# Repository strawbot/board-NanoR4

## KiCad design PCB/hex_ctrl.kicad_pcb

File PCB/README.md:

# hex_ctrl: KiCad starter project

Generated schematic for the octagonal 24-channel muscle-wire controller (Nano R4 carrier).
Written in KiCad 7 file format so any newer KiCad (including 10) opens it; KiCad will
offer to save in its own format on first save.

## Sheets
- hex_ctrl.kicad_sch  top: Nano R4 (A1), mounting holes H1-H5, sheet links
- power.kicad_sch     supply holes, TVS, reverse-protection P-FET, bulk C, VIN_S divider (refs 1000+)
- logic.kicad_sch     3 x 74HC595 gate-drive chain (OE tied to GND), SCK/RCLK series resistors (refs 1100+)
- imu.kicad_sch       ICM-42688-P on the Nano's 3.3 V I2C bus, SDA/SCL solder pads and SWD access holes (refs 1200+)
- group.kicad_sch     used 3 times (A, B, C): RSENSE + ISNS option, two limb sheets (refs 700/800/900+)
- limb.kicad_sch      used 6 times (L1..L6): 4 channels + 5 wire holes (refs 100..600+)

Group A = limbs L1 + L2, B = L3 + L4, C = L5 + L6.

## Supply and output enable (rev 2)
- The rail after reverse protection is called **VIN** (it was +10V). It is the 21 V test supply; any Vin works as long as
  the parts below are rated for it (see the supply-rating note in the power sheet). VIN_S = Vin x 18k/118k (R1003 is
  18k, was 47k), 3.2 V at 21 V, to ADC A3.
- Supply ratings at 21 V: D1001 is SMAJ24A (24 V standoff; clamps near 39 V, above the 30 V Vds of the AO3401A and
  AO3400A, so it only absorbs moderate surges). C1001 is 100uF 35 V polymer (7343-43 case, same pads as the old
  7343-31); C1002/C1003 are 10uF 50 V X7R 1206 (a 25 V X5R loses most of its capacitance at 21 V; a 22uF 50 V part
  would need a 1210). D1002 (BZT52C10, 10 V zener, gate to source) holds the P-FET's Vgs at -10 V for any Vin; the
  AO3401A is rated +/-12 V. Check the Nano's VIN limit against Vin.
- The keep-alive output-enable circuit (KA, C1104, D1101, D1102, C1105, R1101, R1102, Q1101, JP1101) is gone. OE on all
  three 74HC595s is tied to GND, so the outputs are always enabled; the gate guard on every channel (CAC / RPD / BAT54)
  keeps a stuck-high output from holding a MOSFET on.

## Wire-hole labels
Each limb hole (J101-J601) has its own label (W1-W4, + for Vin) on both silkscreen faces, outboard of the hole between it
and the board edge (generator/silk_limbs.py; rerun it after moving a limb connector). It replaced the old one-string-per-limb
text from the hexagon generator, which was nowhere near the octagon's holes, and the stale "+10V GND" text.

## IMU interrupt
IMU INT1 (3.3 V logic) goes to Nano D2 (5 V logic) through a one-transistor level shifter: Q1201 (2N7002, gate on +3V3)
with R1204 pulling the IMU side up to +3V3 and R1205 pulling the Nano side (IMU_INT_5V) up to +5V. TP1201 stays on the
IMU side. Nano D2 is therefore no longer a spare pin.

## Schematic layout
Each sheet is drawn as a wired, left-to-right flow (protection chain on power, the SER chain and clock trunks on
logic, gate -> R -> C -> FET -> wire hole on each limb), and the top sheet is a block diagram: the Nano, the power,
logic, IMU and group blocks, with every signal (SER, SCK, RCLK, the 24 gate lines, ISNS, VIN_S, UART) drawn as a
wire between blocks. The power rails are shown as a legend on that sheet. The layout comes from
generator/build2.py; generator/README_generator.md describes how it is regenerated and checked against the
original netlist (net for net, pin for pin).

## Design rules
hex_ctrl.kicad_dru (Board Setup > Custom Rules) adds: 0.125 mm pad clearance inside the
IMU footprint only; 0.4 mm min / 0.6 mm preferred width for the supply rail (VIN), GND, VIN_RAW, the wire
nets (W1..W4) and the SRC buses; 0.25 mm for the ISNS sense lines.

## Pre-placed board
hex_ctrl.kicad_pcb is placed and routed (72 mm octagon with the front 7 mm sliced off, 2 layers, 0.8 mm), with every
footprint linked to its schematic symbol and every pad on its net. Open it and press F8
to confirm it matches the schematic. oct_place.py regenerates the placement; hex_place.py
is the retired 63 mm hexagon version, kept for reference. The octagon exists because the
autorouter only routes at 0/45/90 degrees and the 60 degree limbs of the hexagon left 18
wire nets unrouted. The six limbs sit on the edges at 0/45/135/180/225/315 deg; the front
(USB/Nano) and rear edges carry no limb. The front strip holds nothing but the Nano's USB end, so
FRONT_CUT in oct_place.py (7 mm) trims it and the Nano overhangs the board by about 4 mm; its
silkscreen outline in the A1 footprint is left open at that end. 7 mm is the limit: at 8 mm the
limb 3 wire tracks come within 0.39 mm of the new edge (rule 0.5 mm). The cut saves roughly
260 mm2 of board, about 0.4 g.

## Getting to a board (manual route)
1. Open hex_ctrl.kicad_pro. Check the sheets (the text notes flag items to verify).
2. Run Inspect > Electrical Rules Checker. Expected: no errors; unconnected pins are
   marked with no-connect flags.
3. Open the PCB editor, set the board to 2 layers / 0.8 mm (Board Setup), then
   Tools > Update PCB from Schematic (F8).
4. Tools > Scripting Console:  exec(open(r"<path>/hex_place.py").read())
   Draws the hexagon and places every part in its zone (limbs on the edges,
   group parts at their vertices, power at 210 deg,
   IMU at the centre, Nano flipped to the bottom). Checked for courtyard overlaps.

## Board size
oct_place.py uses A = 72 mm across flats. The per-gate guard (CAC + BAT54 on every
channel) made each limb block deeper, and the shorter octagon edges leave less margin at
the vertices; 72 mm placed with the 15 listed courtyard nudges. Change A at the top of
oct_place.py and re-derive the NUDGE table if you resize.

## Designators on the board
Connector (J*) and test point (TP*) designators are on the front silkscreen so they can be read on the
assembled board (generator/silk_designators.py places each at the nearest free spot; rerun it after moving
parts). All other designators and all values stay on F.Fab, which is not part of the manufacturing outputs.
TP1202-TP1208 (the Nano holes) have function labels instead: SCL, SDA, CLK, DIO, RST, GND, 3V3.

## Nano interface (I2C pads, SWD access holes, UART)
J1201 (Qwiic placeholder) was removed. Instead:
- Power and ground come from the Nano castellation: A1 pad 17 (3V3) drives the +3V3 rail,
  pad 4 is GND.
- TP1202 (SCL) and TP1203 (SDA) are 1.6 mm pads with 1.0 mm plated holes
  (hex_ctrl:Nano_Hole_Pad) that sit under the two through-holes either side of the Nano's
  Qwiic connector. Solder a short pin or wire through each hole to the Nano.
- TP1204-TP1208 (SWDIO, SWCLK, NRST, GND, 3V3; silkscreen DIO, CLK, RST, GND, 3V3) are the same
  hole pad, placed over the Nano's SWD test pads. Those pads are on the Nano's underside, which
  faces this board, under the Qwiic connector. Use a pogo pin or solder a wire down the hole
  to reach a pad. SWDIO, SWCLK and NRST have no connection on this board (one-pad nets);
  GND goes to GND, 3V3 to +3V3.
- J1001 is now 1x04: pin 1 VIN_RAW, pin 2 GND, pin 3 TX (Nano D1), pin 4 RX (Nano D0). GND is
  shared with the power input, so pins 2-4 form a GND / TX / RX UART header. Do not plug a
  UART cable onto pins 1-2.

The hole positions come from Arduino's ABX00142 Altium CAD, which is older than the Nano in
hand (its test pad labelled 3V3 is on the +5V net there; measured as 3V3 on the real board).
Measure the real Nano and move TP1202-TP1208 if they differ: mapping and offsets are in
oct_place.py (nano_xy) and generator/nano_iface_pcb.py. The silkscreen labels are board text
from that script. Schematic edits are in generator/nano_iface_sch.py (run once; it edits the
.kicad_sch files in place so footprint links survive).

## Verify before layout
- Nano R4: D9 (RCLK) must be a GPT timer output. D6 (formerly KA) is unused.
- Footprint A1 is hex_ctrl:Arduino_Nano_R4_Castellated (project library): 30 SMD pads
  for soldering the Nano flat on the bottom by its castellated edge. Pad size and offset
  are estimates; check against the real Nano. The Qwiic header placeholder J1201 is gone;
  see "Nano interface" above.
- ICM-42688-P: RESV pins and INT2/FSYNC left unconnected; confirm with the datasheet.
  Confirm the LGA-14 footprint pad order against the datasheet land pattern.
- DNP parts: C701/C801/C901 (ISNS filter), R1202/R1203 (I2C pull-ups).

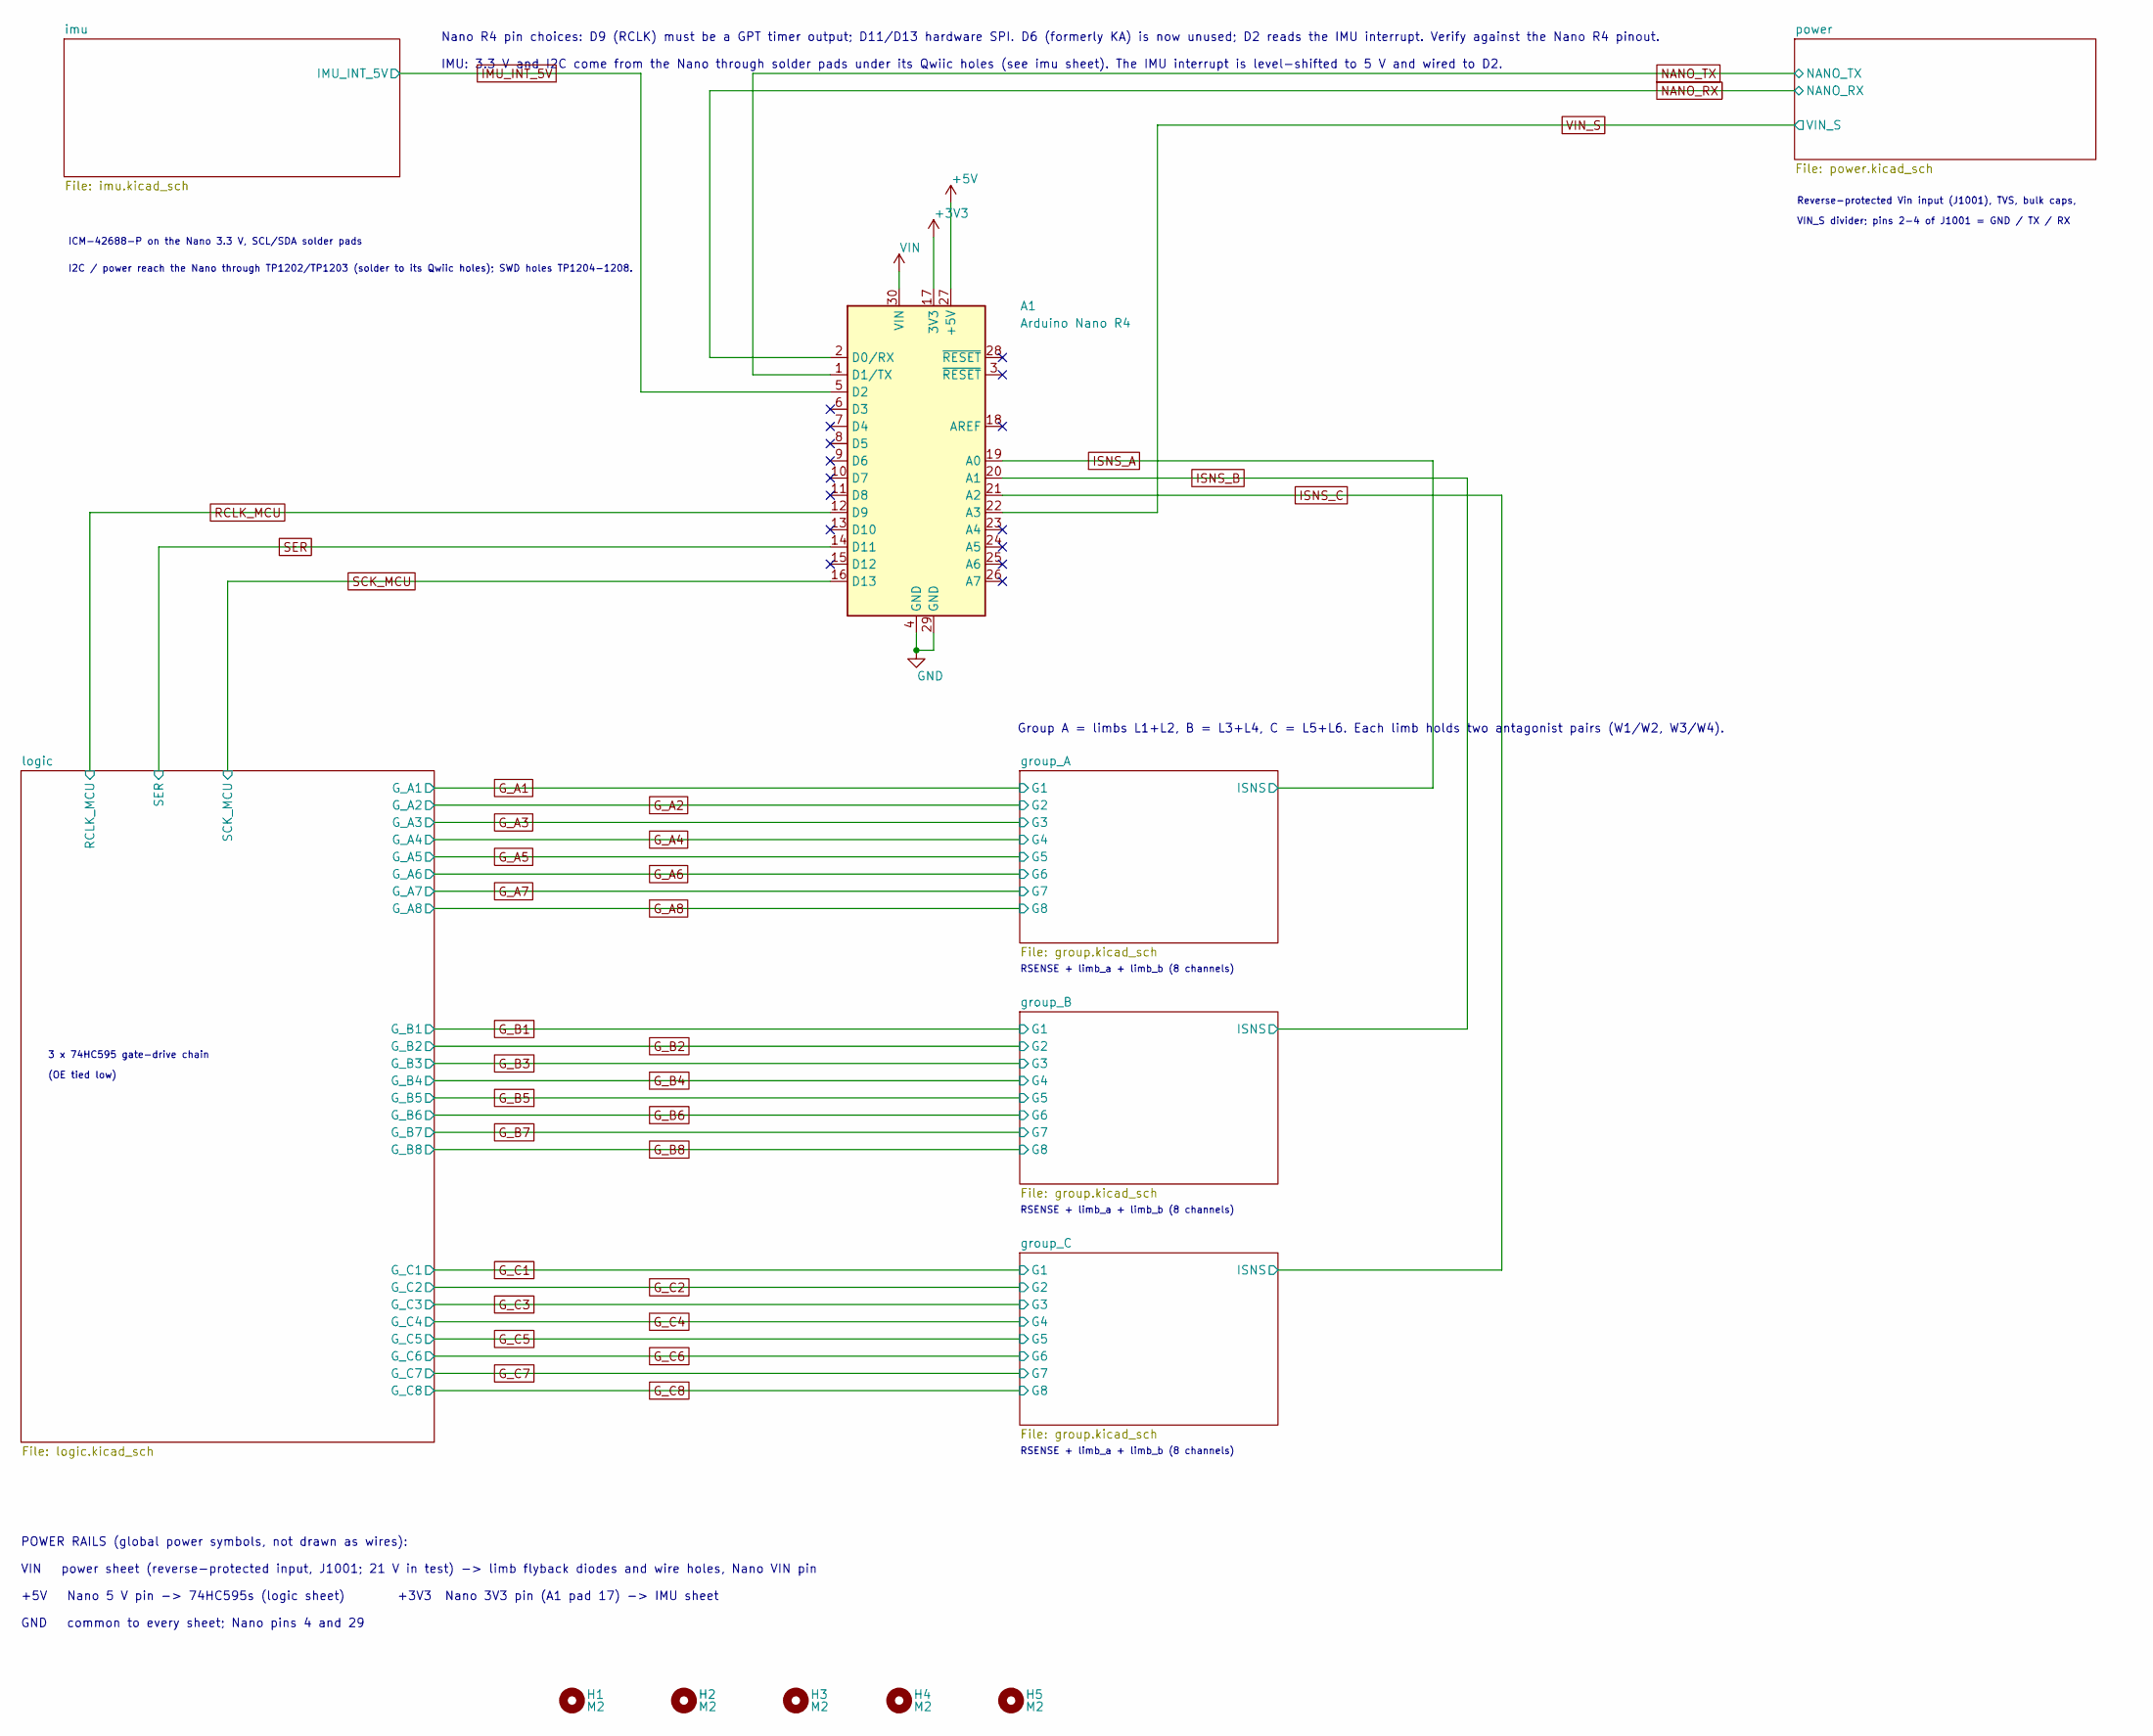
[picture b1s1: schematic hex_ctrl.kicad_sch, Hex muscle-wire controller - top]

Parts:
A1: Arduino Nano R4; Arduino_Nano_R4_Castellated
H1, H2, H3, H4, H5: M2; MountingHole_2.2mm_M2

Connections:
+3V3: A1.17 (3V3); also elsewhere on the board
GND: A1.4 (GND), A1.29 (GND); also elsewhere on the board
IMU_INT_5V: A1.5 (D2); also elsewhere on the board
ISNS_A: A1.19 (A0); also elsewhere on the board
ISNS_B: A1.20 (A1); also elsewhere on the board
ISNS_C: A1.21 (A2); also elsewhere on the board
NANO_RX: A1.2 (D0/RX); also elsewhere on the board
NANO_TX: A1.1 (D1/TX); also elsewhere on the board
RCLK_MCU: A1.12 (D9); also elsewhere on the board
SCK_MCU: A1.16 (D13); also elsewhere on the board
SER: A1.14 (D11); also elsewhere on the board
VIN: A1.30 (VIN); also elsewhere on the board
VIN_S: A1.22 (A3); also elsewhere on the board

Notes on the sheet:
Reverse-protected Vin input (J1001), TVS, bulk caps,
VIN_S divider; pins 2-4 of J1001 = GND / TX / RX
ICM-42688-P on the Nano 3.3 V, SCL/SDA solder pads
3 x 74HC595 gate-drive chain
(OE tied low)
RSENSE + limb_a + limb_b (8 channels)
Nano R4 pin choices: D9 (RCLK) must be a GPT timer output; D11/D13 hardware SPI. D6 (formerly KA) is now unused; D2 reads the IMU interrupt. Verify against the Nano R4 pinout.
IMU: 3.3 V and I2C come from the Nano through solder pads under its Qwiic holes (see imu sheet). The IMU interrupt is level-shifted to 5 V and wired to D2.
I2C / power reach the Nano through TP1202/TP1203 (solder to its Qwiic holes); SWD holes TP1204-1208.
Group A = limbs L1+L2, B = L3+L4, C = L5+L6. Each limb holds two antagonist pairs (W1/W2, W3/W4).
POWER RAILS (global power symbols, not drawn as wires):
VIN power sheet (reverse-protected input, J1001; 21 V in test) -> limb flyback diodes and wire holes, Nano VIN pin
+5V Nano 5 V pin -> 74HC595s (logic sheet) +3V3 Nano 3V3 pin (A1 pad 17) -> IMU sheet
GND common to every sheet; Nano pins 4 and 29

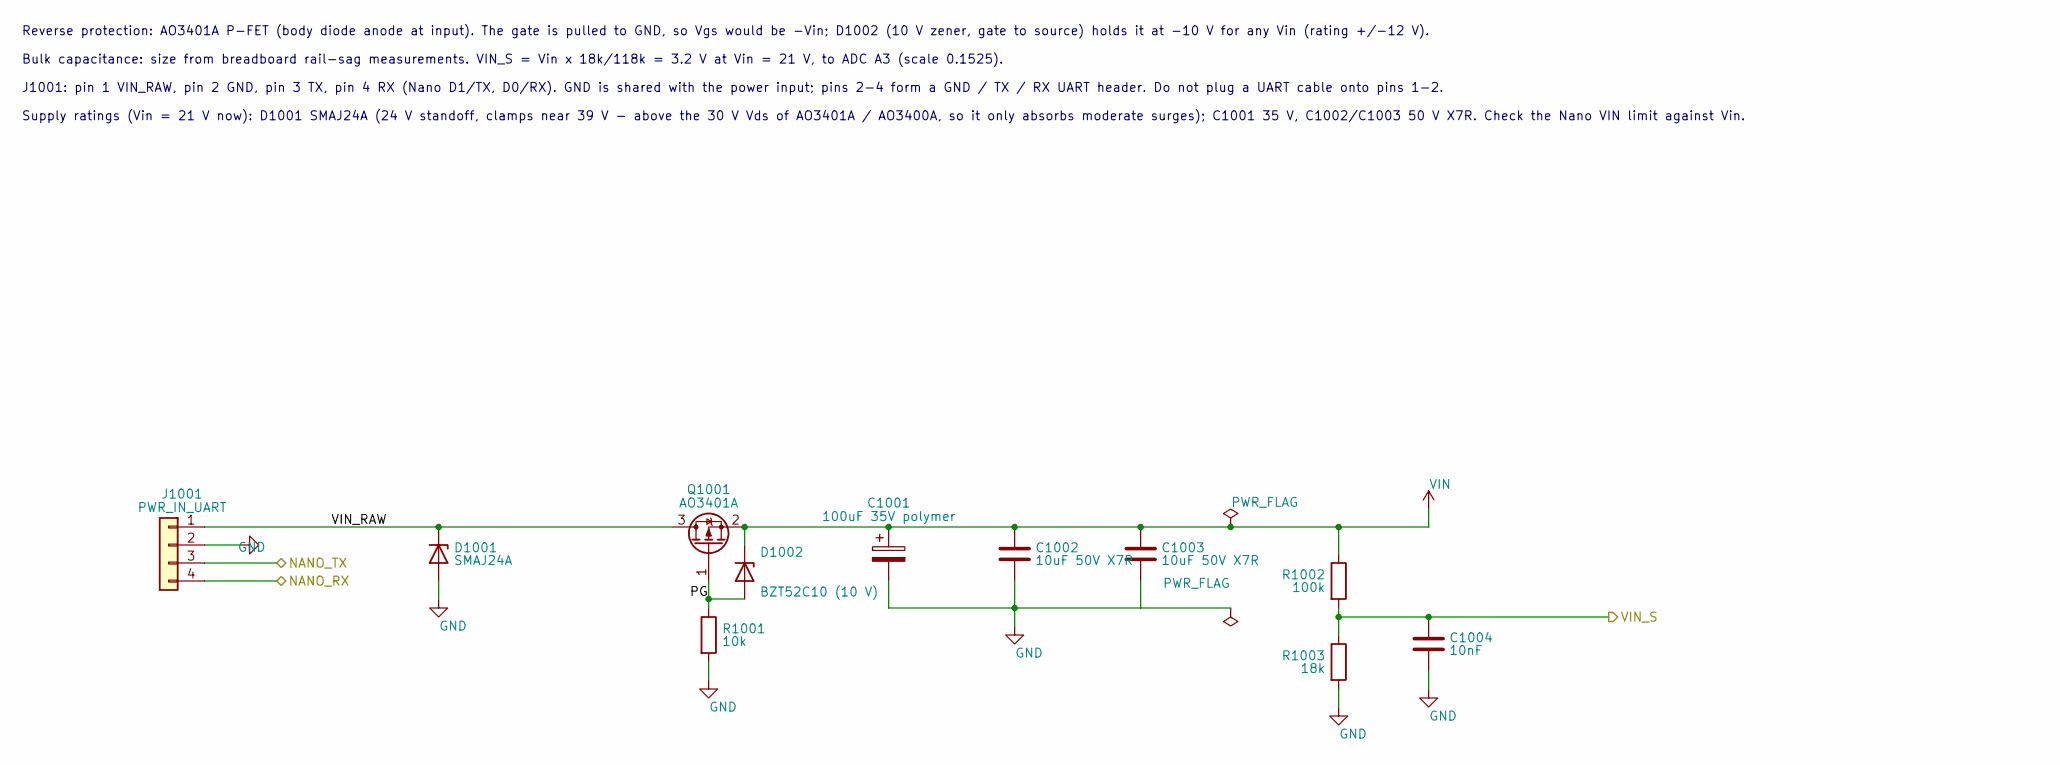
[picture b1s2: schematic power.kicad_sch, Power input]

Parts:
C1001: 100uF 35V polymer; CP_EIA-7343-43_Kemet-X
C1002, C1003: 10uF 50V X7R; C_1206_3216Metric
C1004: 10nF; C_0402_1005Metric
D1001: SMAJ24A; D_SMA
D1002: BZT52C10 (10 V); D_SOD-123
J1001: PWR_IN_UART; PinHeader_1x04_P2.54mm_Vertical
Q1001: AO3401A; SOT-23
R1001: 10k; R_0402_1005Metric
R1002: 100k; R_0402_1005Metric
R1003: 18k; R_0402_1005Metric

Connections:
/power/PG: D1002.2 (A), Q1001.1 (G), R1001.1
/power/VIN_RAW: D1001.1 (K), J1001.1, Q1001.3 (D)
GND: C1001.2, C1002.2, C1003.2, C1004.2, D1001.2 (A), J1001.2, R1001.2, R1003.2; also elsewhere on the board
NANO_RX: J1001.4; also elsewhere on the board
NANO_TX: J1001.3; also elsewhere on the board
VIN: C1001.1, C1002.1, C1003.1, D1002.1 (K), Q1001.2 (S), R1002.1; also elsewhere on the board
VIN_S: C1004.1, R1002.2, R1003.1; also elsewhere on the board

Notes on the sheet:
Reverse protection: AO3401A P-FET (body diode anode at input). The gate is pulled to GND, so Vgs would be -Vin; D1002 (10 V zener, gate to source) holds it at -10 V for any Vin (rating +/-12 V).
Bulk capacitance: size from breadboard rail-sag measurements. VIN_S = Vin x 18k/118k = 3.2 V at Vin = 21 V, to ADC A3 (scale 0.1525).
Supply ratings (Vin = 21 V now): D1001 SMAJ24A (24 V standoff, clamps near 39 V - above the 30 V Vds of AO3401A / AO3400A, so it only absorbs moderate surges); C1001 35 V, C1002/C1003 50 V X7R. Check the Nano VIN limit against Vin.
J1001: pin 1 VIN_RAW, pin 2 GND, pin 3 TX, pin 4 RX (Nano D1/TX, D0/RX). GND is shared with the power input; pins 2-4 form a GND / TX / RX UART header. Do not plug a UART cable onto pins 1-2.

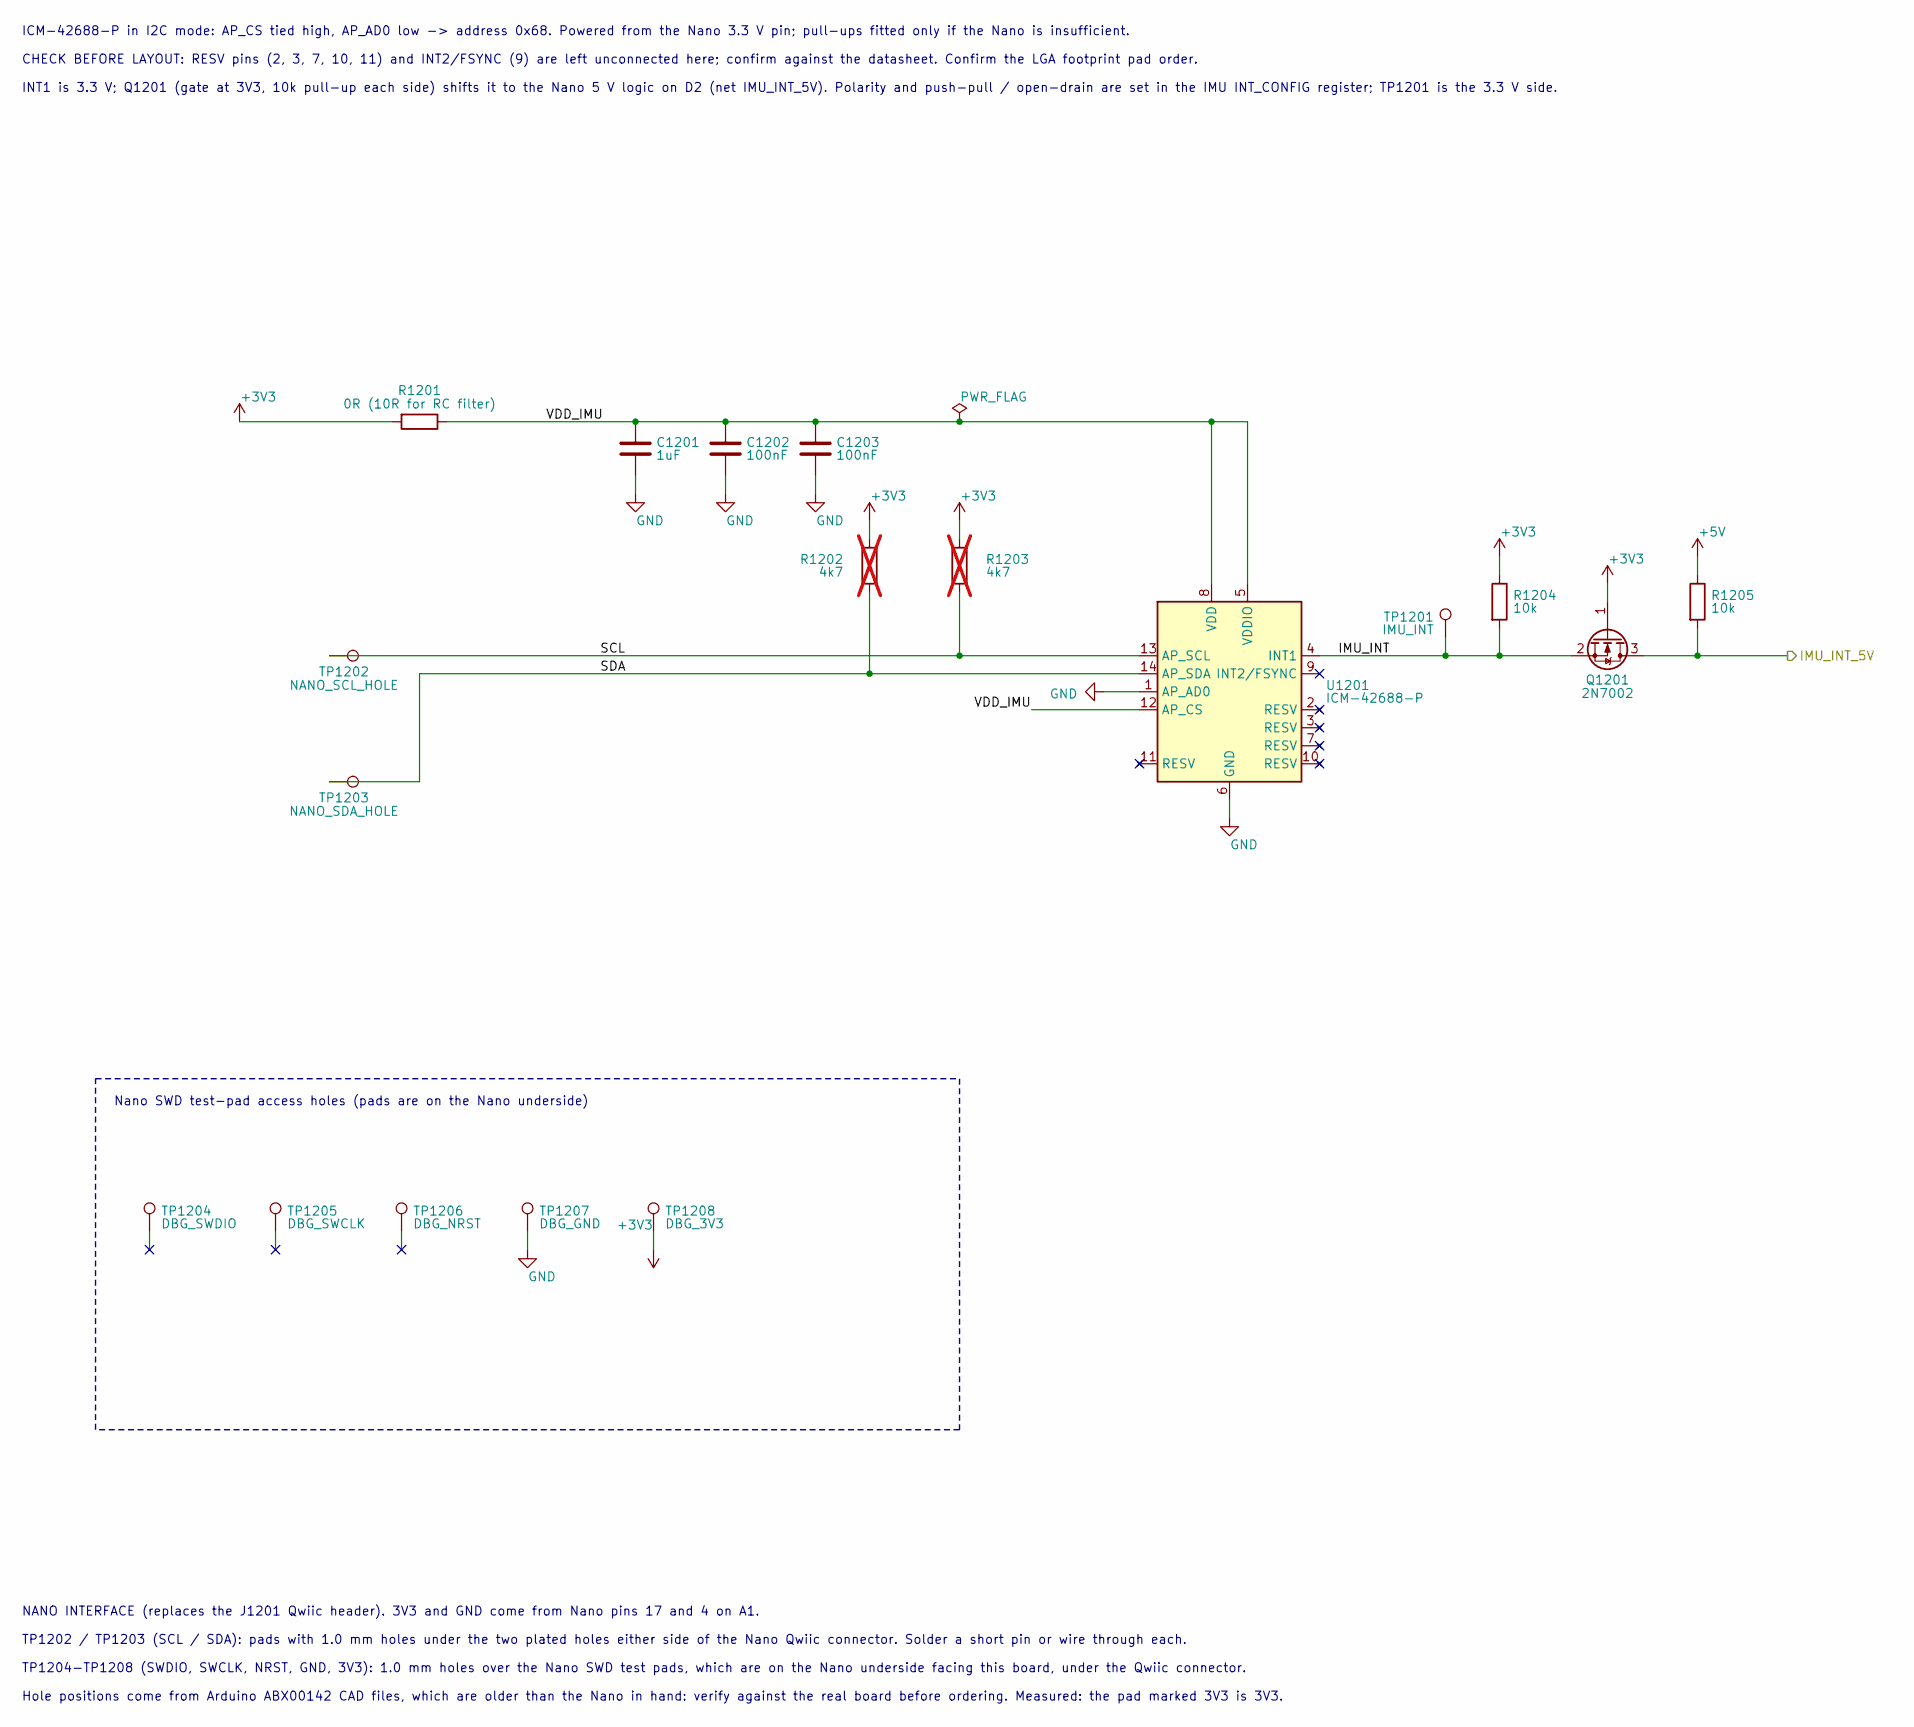
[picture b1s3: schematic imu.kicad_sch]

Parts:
C1201: 1uF; C_0402_1005Metric
C1202, C1203: 100nF; C_0402_1005Metric
Q1201: 2N7002; SOT-23
R1201: 0R (10R for RC filter); R_0402_1005Metric
R1202, R1203: 4k7; R_0402_1005Metric; not fitted
R1204, R1205: 10k; R_0402_1005Metric
TP1201: IMU_INT; TestPoint_Pad_D1.0mm
TP1202: NANO_SCL_HOLE; Nano_Hole_Pad
TP1203: NANO_SDA_HOLE; Nano_Hole_Pad
TP1204: DBG_SWDIO; Nano_Hole_Pad
TP1205: DBG_SWCLK; Nano_Hole_Pad
TP1206: DBG_NRST; Nano_Hole_Pad
TP1207: DBG_GND; Nano_Hole_Pad
TP1208: DBG_3V3; Nano_Hole_Pad
U1201: ICM-42688-P; LGA-14_3x2.5mm_P0.5mm_LayoutBorder3x4y

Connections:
+3V3: Q1201.1 (G), R1201.2, R1202.1, R1203.1, R1204.1, TP1208.1; also elsewhere on the board
/imu/IMU_INT: Q1201.2 (S), R1204.2, TP1201.1, U1201.4 (INT1)
/imu/SCL: R1203.2, TP1202.1, U1201.13 (AP_SCL)
/imu/SDA: R1202.2, TP1203.1, U1201.14 (AP_SDA)
/imu/VDD_IMU: C1201.1, C1202.1, C1203.1, R1201.1, U1201.5 (VDDIO), U1201.8 (VDD), U1201.12 (AP_CS)
GND: C1201.2, C1202.2, C1203.2, TP1207.1, U1201.1 (AP_AD0), U1201.6 (GND); also elsewhere on the board
IMU_INT_5V: Q1201.3 (D), R1205.2; also elsewhere on the board

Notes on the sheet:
Nano SWD test-pad access holes (pads are on the Nano underside)
ICM-42688-P in I2C mode: AP_CS tied high, AP_AD0 low -> address 0x68. Powered from the Nano 3.3 V pin; pull-ups fitted only if the Nano is insufficient.
CHECK BEFORE LAYOUT: RESV pins (2, 3, 7, 10, 11) and INT2/FSYNC (9) are left unconnected here; confirm against the datasheet. Confirm the LGA footprint pad order.
INT1 is 3.3 V; Q1201 (gate at 3V3, 10k pull-up each side) shifts it to the Nano 5 V logic on D2 (net IMU_INT_5V). Polarity and push-pull / open-drain are set in the IMU INT_CONFIG register; TP1201 is the 3.3 V side.
NANO INTERFACE (replaces the J1201 Qwiic header). 3V3 and GND come from Nano pins 17 and 4 on A1.
TP1202 / TP1203 (SCL / SDA): pads with 1.0 mm holes under the two plated holes either side of the Nano Qwiic connector. Solder a short pin or wire through each.
TP1204-TP1208 (SWDIO, SWCLK, NRST, GND, 3V3): 1.0 mm holes over the Nano SWD test pads, which are on the Nano underside facing this board, under the Qwiic connector.
Hole positions come from Arduino ABX00142 CAD files, which are older than the Nano in hand: verify against the real board before ordering. Measured: the pad marked 3V3 is 3V3.

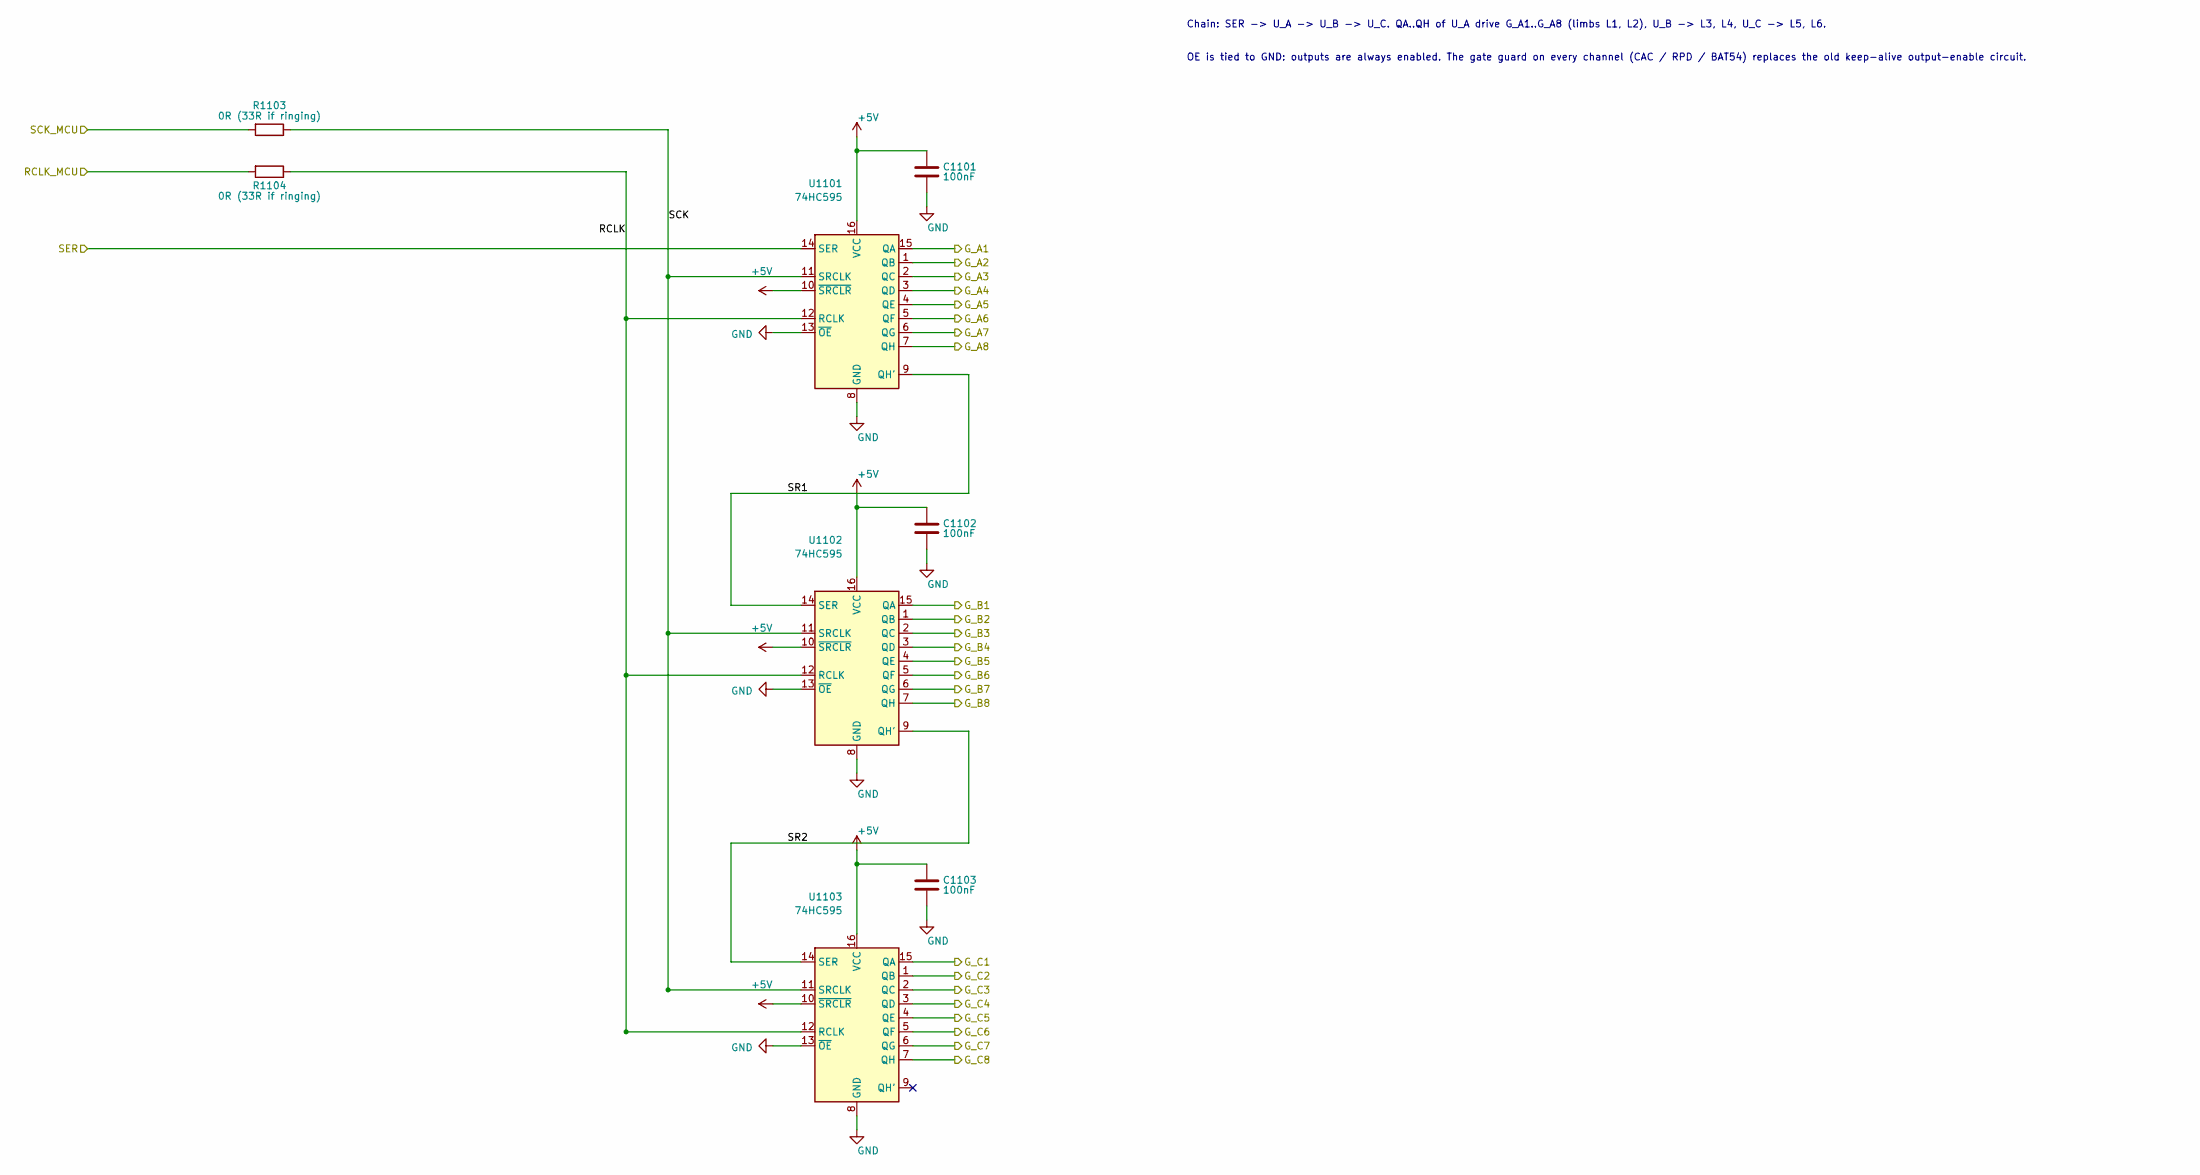
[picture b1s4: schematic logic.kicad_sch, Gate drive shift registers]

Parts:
C1101, C1102, C1103: 100nF; C_0402_1005Metric
R1103, R1104: 0R (33R if ringing); R_0402_1005Metric
U1101, U1102, U1103: 74HC595; TSSOP-16_4.4x5mm_P0.65mm

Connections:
/logic/RCLK: R1104.1, U1101.12 (RCLK), U1102.12 (RCLK), U1103.12 (RCLK)
/logic/SCK: R1103.1, U1101.11 (SRCLK), U1102.11 (SRCLK), U1103.11 (SRCLK)
/logic/SR2: U1102.9 (QH'), U1103.14 (SER)
GND: C1101.2, C1102.2, C1103.2, U1101.8 (GND), U1101.13 (~OE), U1102.8 (GND), U1102.13 (~OE), U1103.8 (GND), U1103.13 (~OE); also elsewhere on the board
G_A1: U1101.15 (QA); also elsewhere on the board
G_A2: U1101.1 (QB); also elsewhere on the board
G_A3: U1101.2 (QC); also elsewhere on the board
G_A4: U1101.3 (QD); also elsewhere on the board
G_A5: U1101.4 (QE); also elsewhere on the board
G_A6: U1101.5 (QF); also elsewhere on the board
G_A7: U1101.6 (QG); also elsewhere on the board
G_A8: U1101.7 (QH); also elsewhere on the board
G_B1: U1102.15 (QA); also elsewhere on the board
G_B2: U1102.1 (QB); also elsewhere on the board
G_B3: U1102.2 (QC); also elsewhere on the board
G_B4: U1102.3 (QD); also elsewhere on the board
G_B5: U1102.4 (QE); also elsewhere on the board
G_B6: U1102.5 (QF); also elsewhere on the board
G_B7: U1102.6 (QG); also elsewhere on the board
G_B8: U1102.7 (QH); also elsewhere on the board
G_C1: U1103.15 (QA); also elsewhere on the board
G_C2: U1103.1 (QB); also elsewhere on the board
G_C3: U1103.2 (QC); also elsewhere on the board
G_C4: U1103.3 (QD); also elsewhere on the board
G_C5: U1103.4 (QE); also elsewhere on the board
G_C6: U1103.5 (QF); also elsewhere on the board
G_C7: U1103.6 (QG); also elsewhere on the board
G_C8: U1103.7 (QH); also elsewhere on the board
RCLK_MCU: R1104.2; also elsewhere on the board
SCK_MCU: R1103.2; also elsewhere on the board
SER: U1101.14 (SER); also elsewhere on the board

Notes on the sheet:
Chain: SER -> U_A -> U_B -> U_C. QA..QH of U_A drive G_A1..G_A8 (limbs L1, L2), U_B -> L3, L4, U_C -> L5, L6.
OE is tied to GND: outputs are always enabled. The gate guard on every channel (CAC / RPD / BAT54) replaces the old keep-alive output-enable circuit.

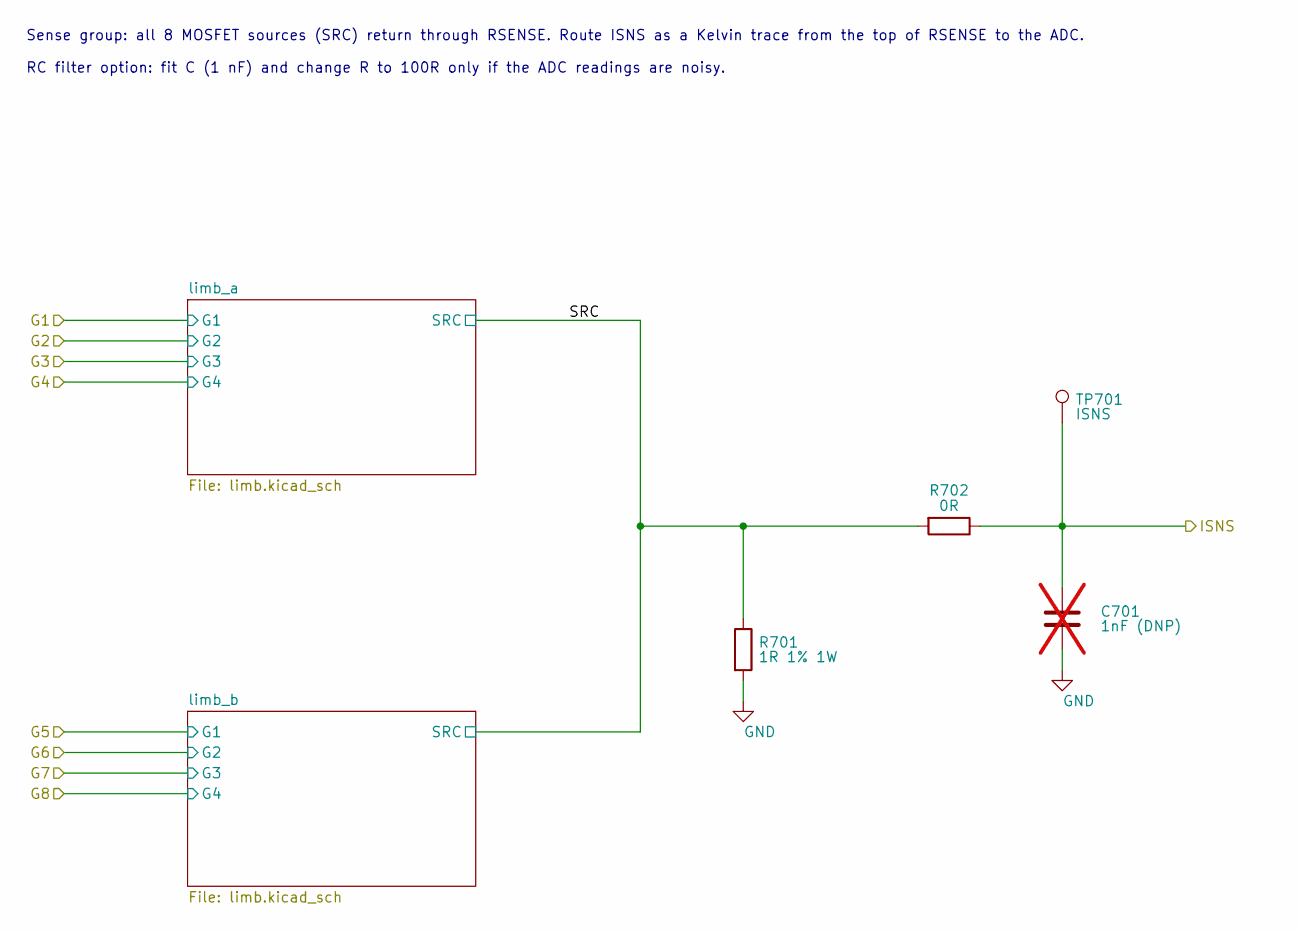
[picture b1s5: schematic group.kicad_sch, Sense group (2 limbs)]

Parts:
C701: 1nF (DNP); C_0402_1005Metric; not fitted
R701: 1R 1% 1W; R_2512_6332Metric
R702: 0R; R_0402_1005Metric
TP701: ISNS; TestPoint_Pad_D1.0mm

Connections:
/group_A/SRC: R701.1, R702.2; also elsewhere on the board
GND: C701.2, R701.2; also elsewhere on the board
ISNS_A: C701.1, R702.1, TP701.1; also elsewhere on the board

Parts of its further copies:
C801, C901: 1nF (DNP); C_0402_1005Metric; not fitted
R801, R901: 1R 1% 1W; R_2512_6332Metric
R802, R902: 0R; R_0402_1005Metric
TP801, TP901: ISNS; TestPoint_Pad_D1.0mm

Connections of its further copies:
/group_B/SRC: R801.1, R802.2; also elsewhere on the board
/group_C/SRC: R901.1, R902.2; also elsewhere on the board
GND: C801.2, C901.2, R801.2, R901.2; also elsewhere on the board
ISNS_B: C801.1, R802.1, TP801.1; also elsewhere on the board
ISNS_C: C901.1, R902.1, TP901.1; also elsewhere on the board

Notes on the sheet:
Sense group: all 8 MOSFET sources (SRC) return through RSENSE. Route ISNS as a Kelvin trace from the top of RSENSE to the ADC.
RC filter option: fit C (1 nF) and change R to 100R only if the ADC readings are noisy.
